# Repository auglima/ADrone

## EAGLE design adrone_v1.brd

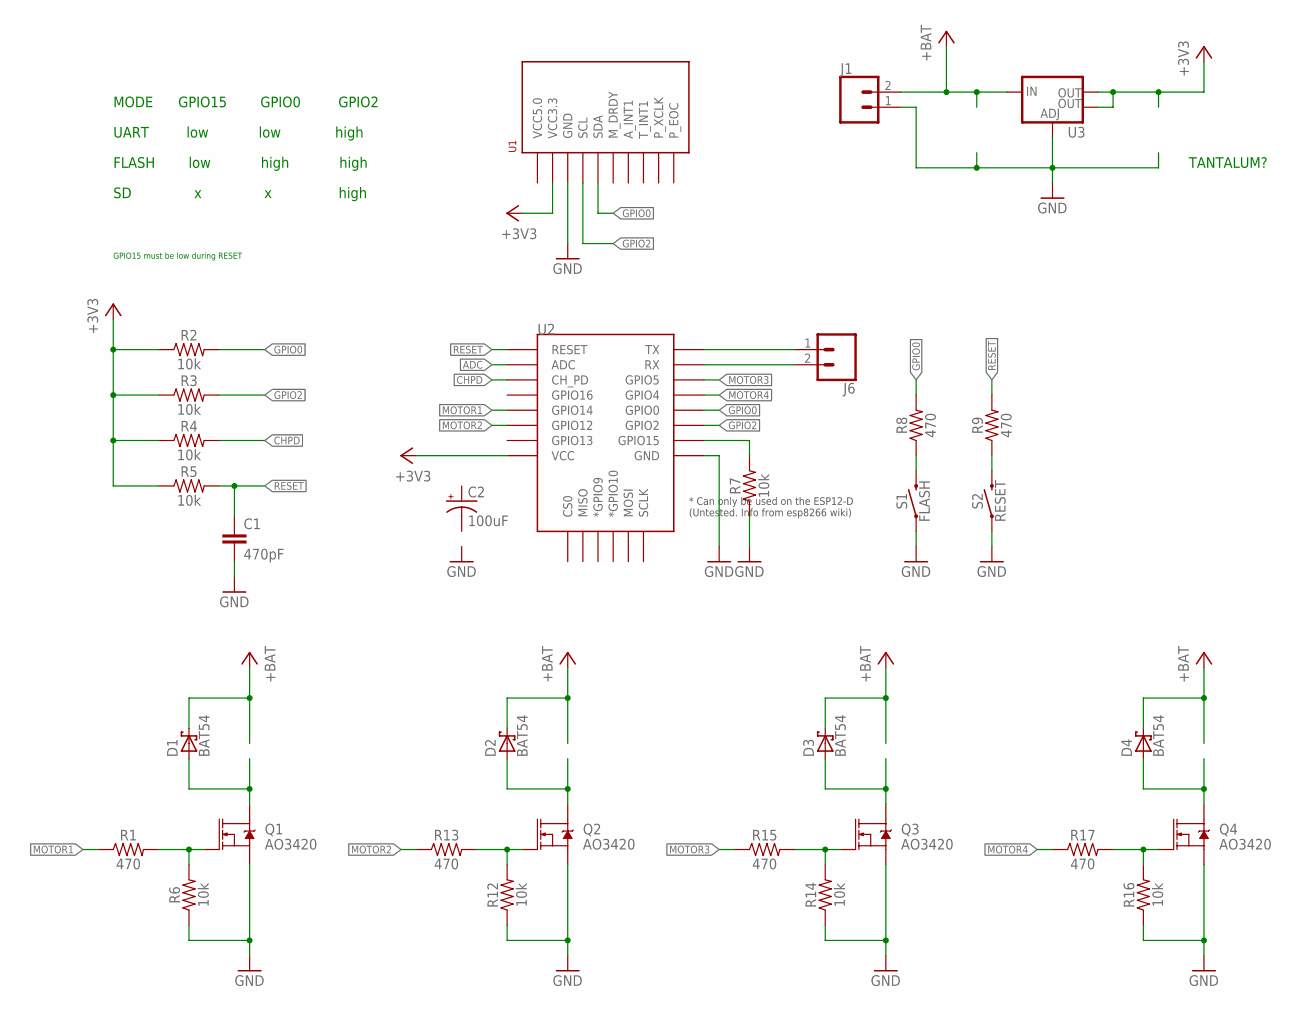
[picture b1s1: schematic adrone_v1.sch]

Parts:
C1: 470pF; 0603
C2: 100uF; EIA7343
D1, D2, D3, D4: BAT54; SOT23
J1, J6: CONN_02; 1X02
Q1, Q2, Q3, Q4: AO3420; SOT23-3
R1, R8, R9, R13, R15, R17: 470; 0603
R2, R3, R4, R5, R6, R7, R12, R14, R16: 10k; 0603
S1: FLASH; TACTILE_SWITCH_SMD_6.0X3.5MM
S2: RESET; TACTILE_SWITCH_SMD_6.0X3.5MM
U1: GY-80_10DOF
U2: ESP12ESMD; ESP12E-SMD
U3: V_REG_LM1117SOT223; SOT223

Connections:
+3V3: R2.1, R3.1, R4.1, R5.1, U1.P$2 (VCC3.3), U2.VCC, U3.2 (OUT), U3.4 (OUT)
+BAT: D1.3 (C), D2.3 (C), D3.3 (C), D4.3 (C), J1.2, U3.3 (IN)
ADC: U2.ADC
CHPD: R4.2, U2.CH_PD
GND: C1.2, J1.1, Q1.2 (S), Q2.2 (S), Q3.2 (S), Q4.2 (S), R6.1, R7.1, R12.1, R14.1, R16.1, S1.1, S2.1, U1.P$3 (GND), U2.GND, U3.1 (ADJ)
GPIO0: R2.2, R8.2, U1.P$5 (SDA), U2.GPIO0
GPIO2: R3.2, U1.P$4 (SCL), U2.GPIO2
MOTOR1: R1.1, U2.GPIO14
MOTOR2: R13.1, U2.GPIO12
MOTOR3: R15.1, U2.GPIO5
MOTOR4: R17.1, U2.GPIO4
unnamed: D1.1 (A), Q1.3 (D)
unnamed: Q2.1 (G), R12.2, R13.2
unnamed: D2.1 (A), Q2.3 (D)
unnamed: Q3.1 (G), R14.2, R15.2
unnamed: R7.2, U2.GPIO15
unnamed: D3.1 (A), Q3.3 (D)
unnamed: Q4.1 (G), R16.2, R17.2
unnamed: J6.2, U2.RXD0 (RX)
unnamed: D4.1 (A), Q4.3 (D)
unnamed: Q1.1 (G), R1.2, R6.2
unnamed: R8.1, S1.2
unnamed: R9.1, S2.2
RESET: C1.1, R5.2, R9.2, U2.RESET
TX: J6.1, U2.TXD0 (TX)

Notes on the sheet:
GPIO15 must be low during RESET
MODE GPIO15 GPIO0 GPIO2
UART low low high
FLASH low high high
TANTALUM?
SD x x high

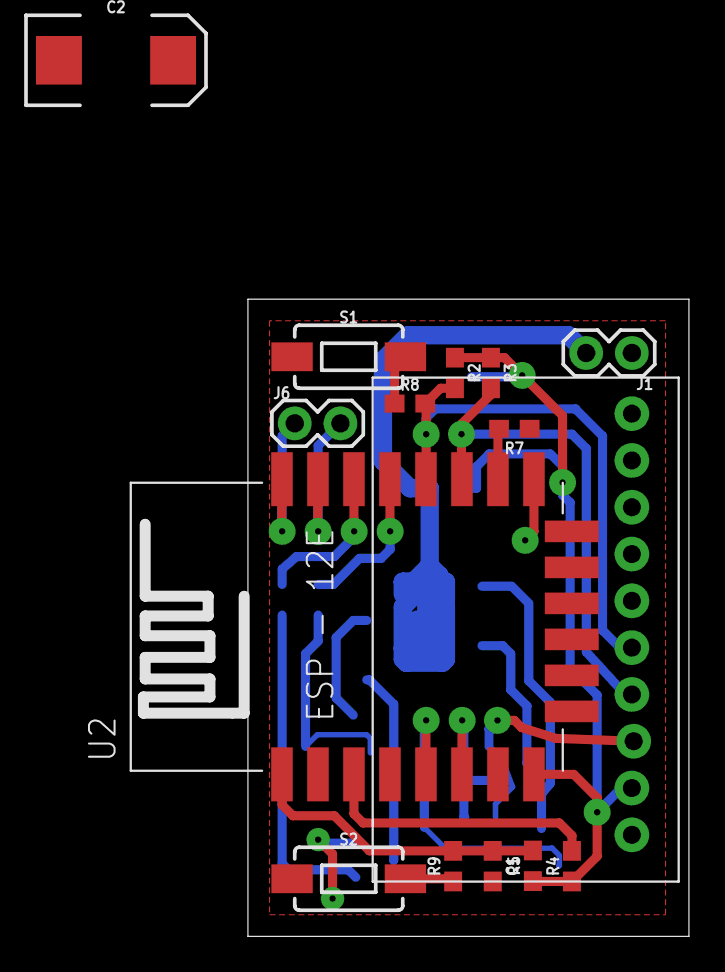
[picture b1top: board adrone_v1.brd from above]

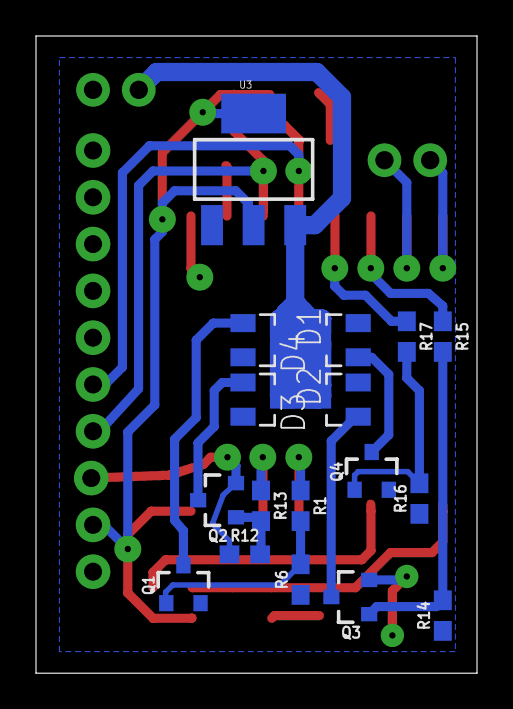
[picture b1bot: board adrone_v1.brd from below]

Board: 2 copper layers, 24.5 x 35.4 mm, 32 parts (17 on the bottom side), 24 nets.

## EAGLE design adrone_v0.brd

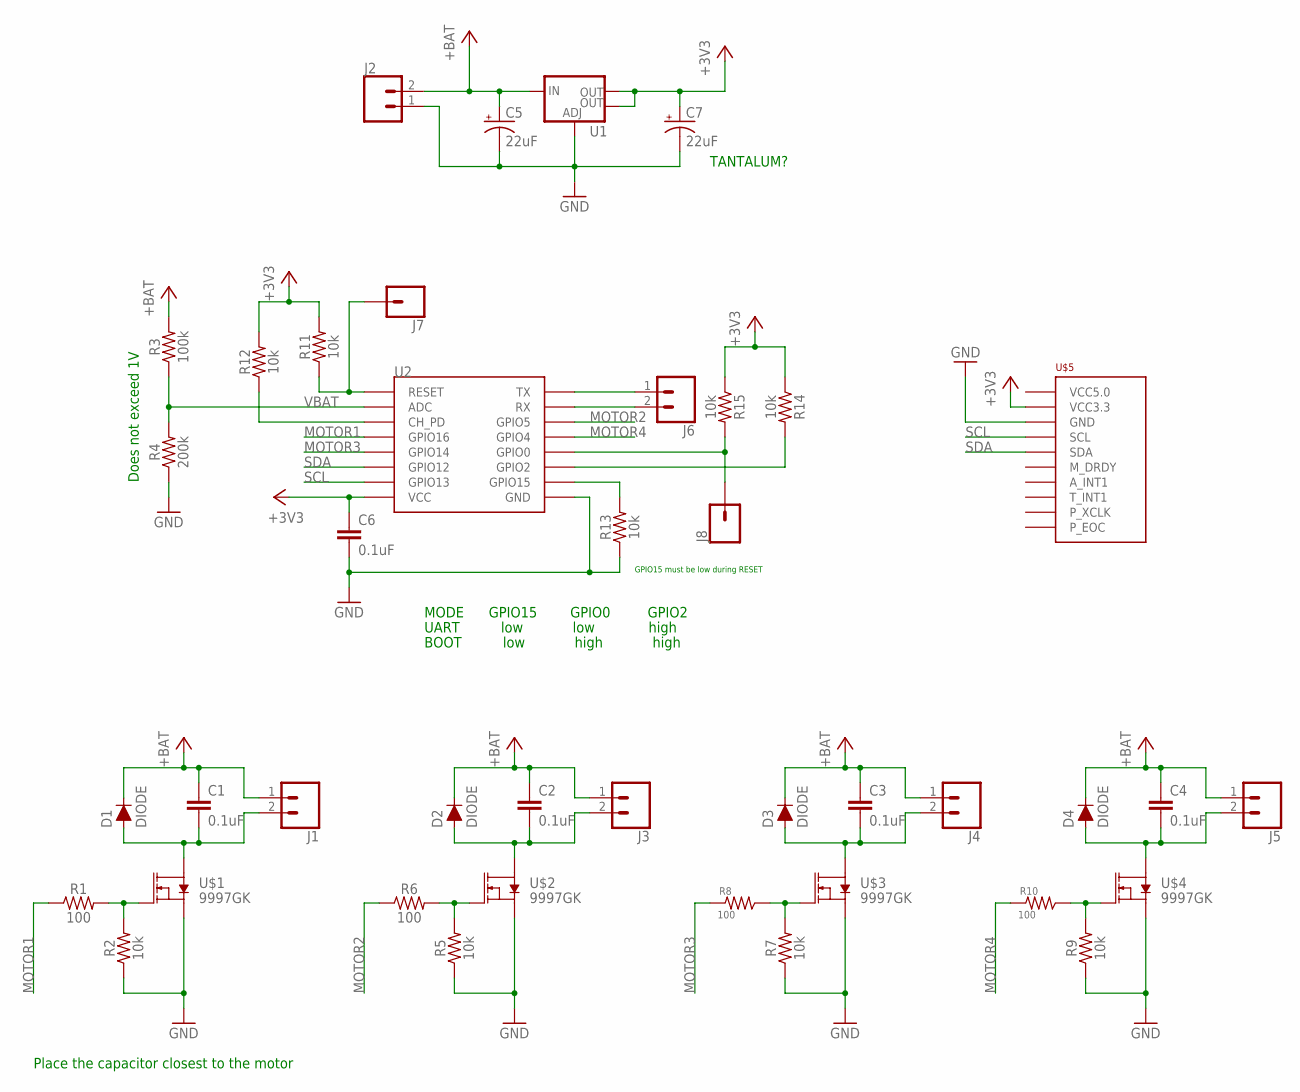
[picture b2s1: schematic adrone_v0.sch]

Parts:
C1, C2, C3, C4, C6: 0.1uF; CAP-PTH-SMALL-KIT
C5, C7: 22uF; CPOL-RADIAL-2.5MM-6.5MM
D1, D2, D3, D4: DIODE; AXIAL-0.1
J1, J2, J3, J4, J5, J6: CONN_02; 1X02
J7, J8: CONN_01; 1X01
R1, R6: 100; AXIAL-0.3
R2, R5, R7, R9, R11, R12, R14, R15: 10k; AXIAL-0.3
R3: 100k; AXIAL-0.3
R4: 200k; AXIAL-0.3
R8, R10: 100; RES-2
R13: 10k; AXIAL-0.1
U1: V_REG_LM1117SOT223; SOT223
U2: ESP12F
U$1, U$2, U$3, U$4: 9997GK; SOT223
U$5: GY-80_10DOF

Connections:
+3V3: C6.1, C7.1 (+), R11.P$2 (2), R12.P$2 (2), R14.P$1 (1), R15.P$1 (1), U1.2 (OUT), U1.4 (OUT), U2.VCC, U$5.P$2 (VCC3.3)
+BAT: C1.1, C2.1, C3.1, C4.1, C5.1 (+), D1.C, D2.C, D3.C, D4.C, J1.1, J2.2, J3.1, J4.1, J5.1, R3.P$2 (2), U1.3 (IN)
ESP-RX: J6.2, U2.RX
ESP-TX: J6.1, U2.TX
GND: C5.2 (-), C6.2, C7.2 (-), J2.1, R2.P$1 (1), R4.P$1 (1), R5.P$1 (1), R7.P$1 (1), R9.P$1 (1), R13.P$1 (1), U1.1 (ADJ), U2.GND, U$1.3 (S), U$2.3 (S), U$3.3 (S), U$4.3 (S), U$5.P$3 (GND)
MOTOR1: R1.P$1 (1), U2.GPIO16
MOTOR2: R6.P$1 (1), U2.GPIO5
MOTOR3: R8.P$1, U2.GPIO14
MOTOR4: R10.P$1, U2.GPIO4
unnamed: R1.P$2 (2), R2.P$2 (2), U$1.1 (G)
unnamed: C1.2, D1.A, J1.2, U$1.2 (D), U$1.4 (D)
unnamed: R14.P$2 (2), U2.GPIO2
unnamed: R5.P$2 (2), R6.P$2 (2), U$2.1 (G)
unnamed: C2.2, D2.A, J3.2, U$2.2 (D), U$2.4 (D)
unnamed: J7.1, R11.P$1 (1), U2.RESET
unnamed: J8.1, R15.P$2 (2), U2.GPIO0
unnamed: R12.P$1 (1), U2.CH_PD
unnamed: R13.P$2 (2), U2.GPIO15
unnamed: R7.P$2 (2), R8.P$2, U$3.1 (G)
unnamed: C3.2, D3.A, J4.2, U$3.2 (D), U$3.4 (D)
unnamed: R9.P$2 (2), R10.P$2, U$4.1 (G)
unnamed: C4.2, D4.A, J5.2, U$4.2 (D), U$4.4 (D)
SCL: U2.GPIO13, U$5.P$4 (SCL)
SDA: U2.GPIO12, U$5.P$5 (SDA)
VBAT: R3.P$1 (1), R4.P$2 (2), U2.ADC

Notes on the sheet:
GPIO15 must be low during RESET
MODE GPIO15 GPIO0 GPIO2
UART low low high
BOOT low high high
Place the capacitor closest to the motor
Does not exceed 1V
TANTALUM?

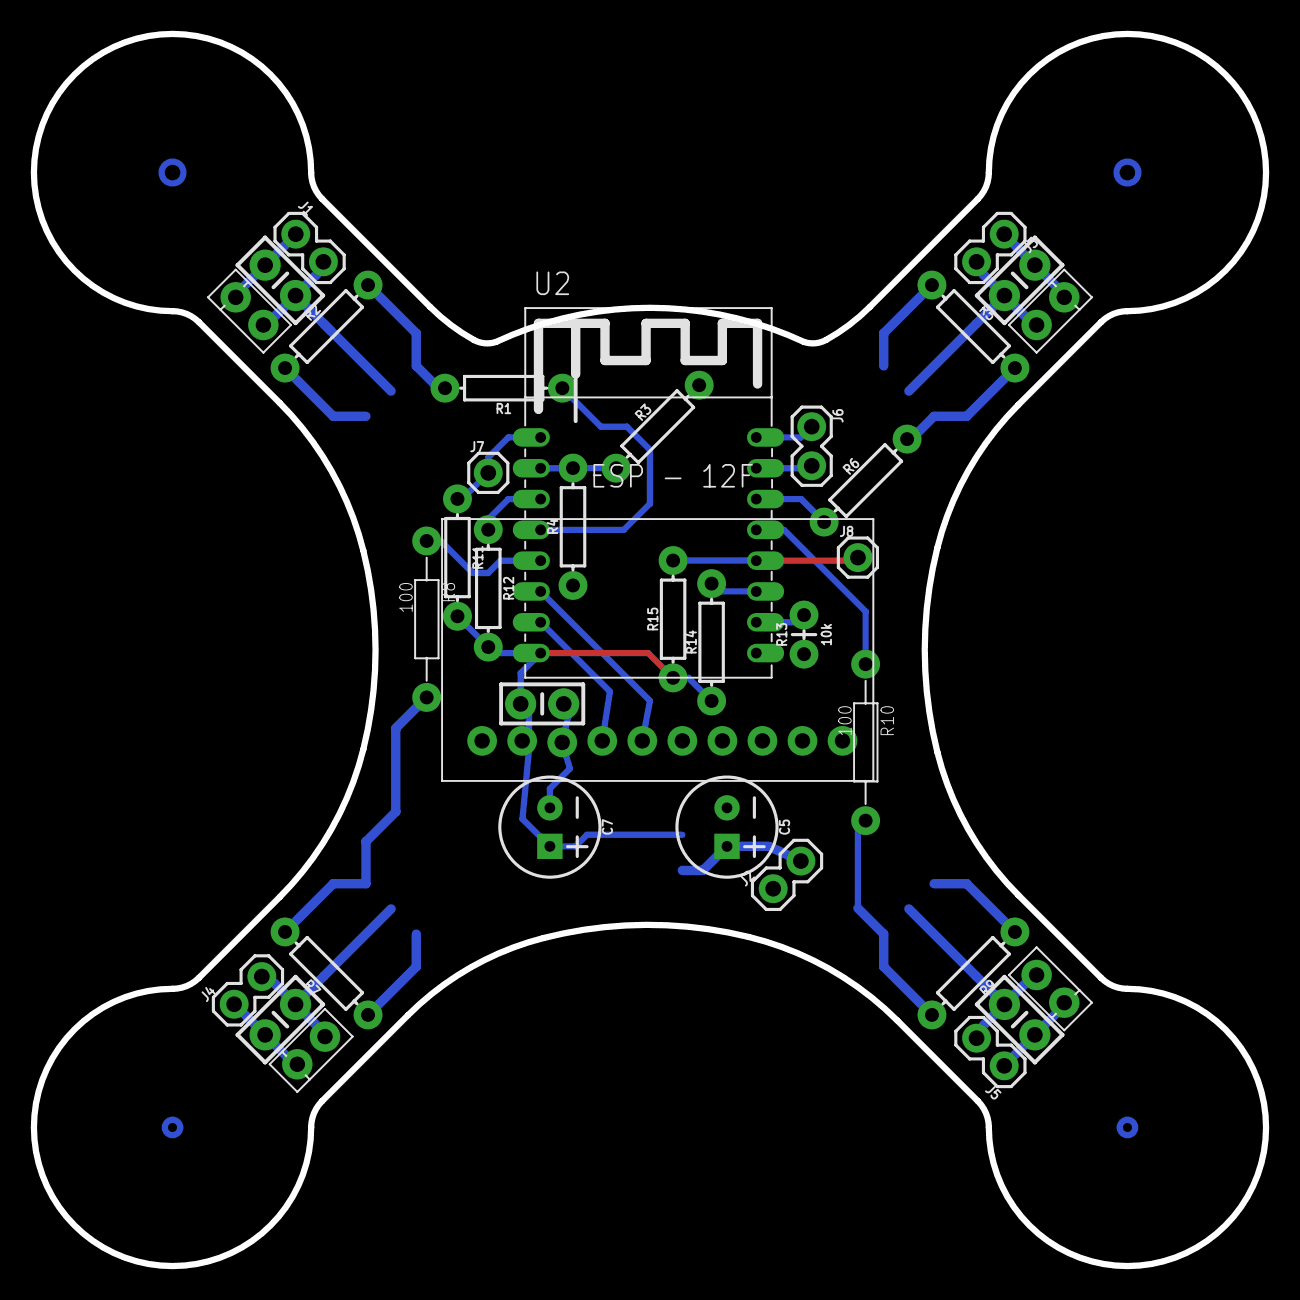
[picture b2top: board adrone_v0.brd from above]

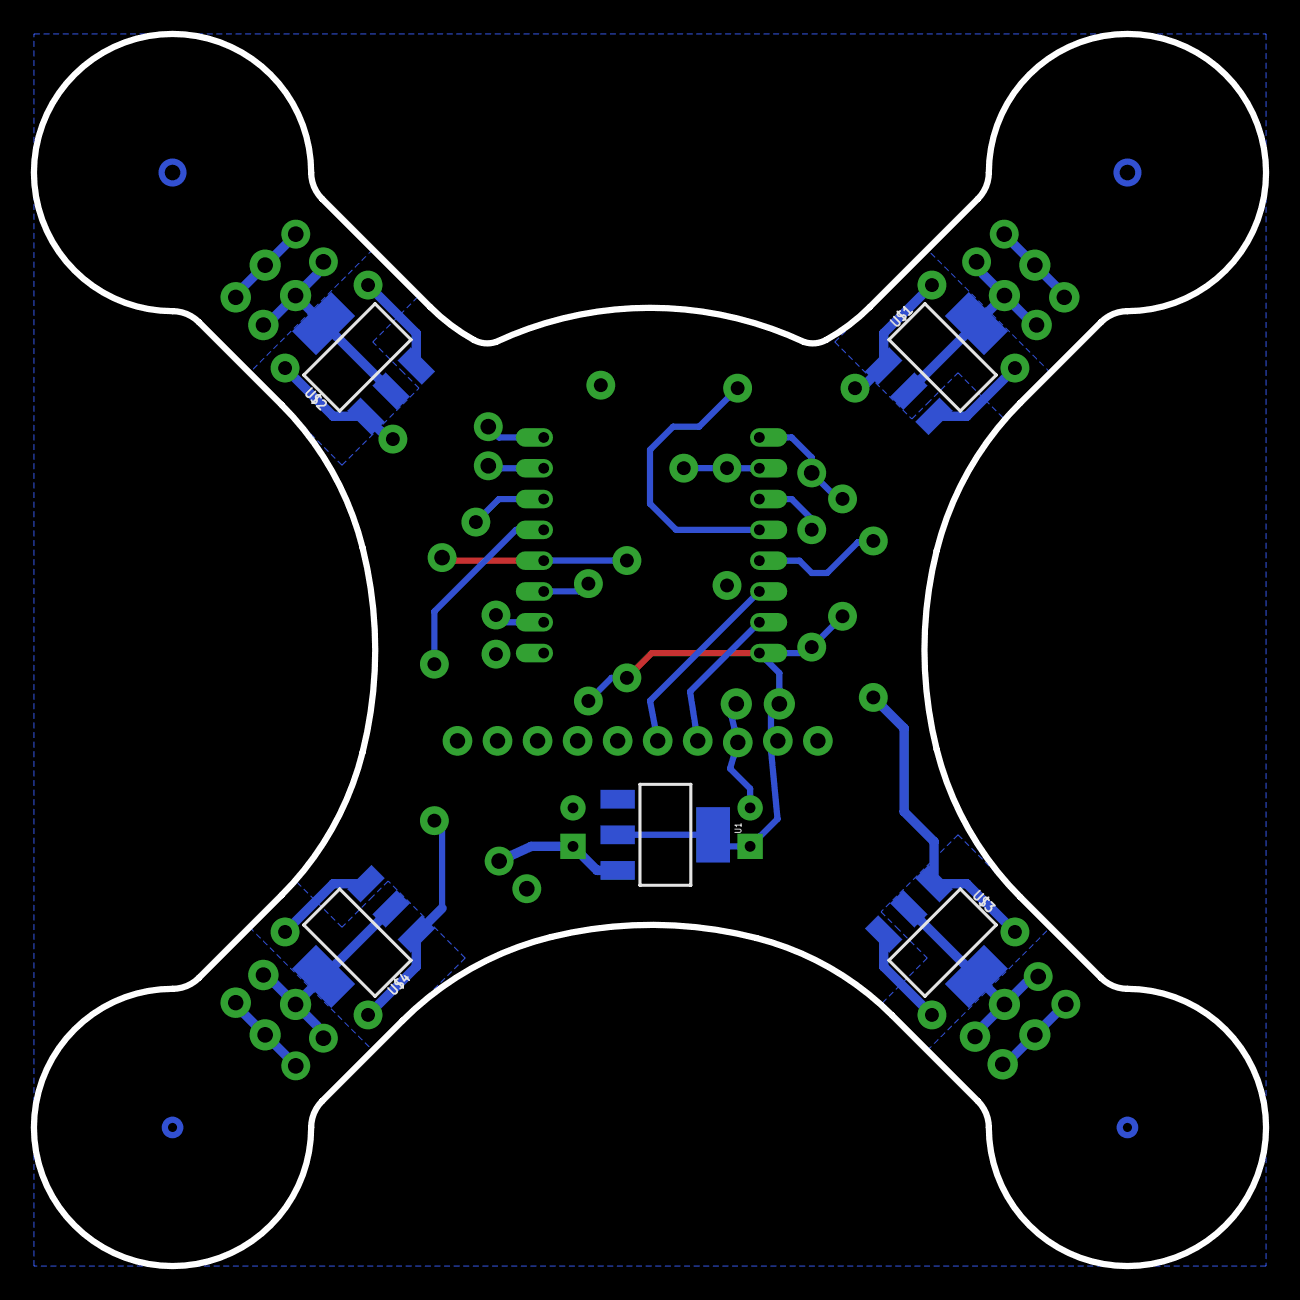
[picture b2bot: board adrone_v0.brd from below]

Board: 2 copper layers, 80.0 x 80.0 mm, 41 parts (5 on the bottom side), 25 nets.

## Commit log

2017-10-13 add file

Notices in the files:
parts and their libraries:
SparkFun-IC-Power: Licensing: Creative Commons ShareAlike 4.0 International - https://creativecommons.org/licenses/by-sa/4.0
